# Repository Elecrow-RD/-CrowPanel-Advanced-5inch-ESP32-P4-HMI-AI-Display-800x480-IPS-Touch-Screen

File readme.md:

### 1, Product picture

### 2, Product version number

|      | Hardware | Software | Remark |
| ---- | -------- | -------- | ------ |
| 1    | V1.0     | V1.0     | latest |

### 3, product information

| **Main Chip-ESP32-P4NRW32**                  |                                                              |
| -------------------------------------------- | ------------------------------------------------------------ |
| CPU/SoC                                      | **ESP32-P4**RISC-V 32-bit dual-core processor for HP systems, running at up to 400 MHz;RISC-V 32-bit single-core processor for LP systems, running at up to 40 MHz |
| System Memory                                | 768 KB L2MEM (HP) 32 KB SRAM (LP) 8 KB TCM 32 MB PSRAM       |
| Memory                                       | 128 KB ROM (HP) 16 KB ROM (LP) 16 MB Flash                   |
| Development Environment                      | ESP-IDF、Arduino IDE                                         |
| **Screen**                                   |                                                              |
| Size                                         | 5.0 inch                                                     |
| Resolution                                   | 800*480                                                     |
| Display Panel                                | IPS Panel                                                    |
| Touch Panel                                  | Capacitive Touch, Single/5-point Touch                       |
| Viewing Angle                                | 178°                                                         |
| Brightness                                   | 400 cd/m²(Typ.)                                              |
| Color Depth                                  | 16.7M (8-bit)                                                |
| **Wireless Communication - Onboard Antenna** |                                                              |
| WiFi                                         | Support 2.4GHz(Wi-Fi6), 802.11a/b/g/n                        |
| Bluetooth                                    | Support Bluetooth 5.3 and BLE                                |
| Other                                        | Zigbee, LoRa, nRF2401, Matter, Thread (**Optional**)         |
| **Interface/Function**                       |                                                              |
| Interface                                    | USB2.0, UART, I2C, GPIO female headers, SD card holder, battery socket, speaker jack, camera header, module female headers, etc. |
| Function                                     | Audio amplifier, battery charge management, USB to UART, dual microphones, dual speakers etc. |
| **Button/LED Indicator**                     |                                                              |
| Reset Button                                 | Yes, press to reset the device                               |
| Boot Button                                  | Yes, press and hold the power button to burn the program     |
| Power Button                                 | Switch On/Off                                                |
| PWR                                          | Device power on/off indication                               |
| CHG                                          | Lithium battery charging status, Low battery state           |
| **Other**                                    |                                                              |
| Installation method                          | All around mounting holes(M3 3.2mm), embedded, shell assembly |
| Operating temperature                        | -20~70 °C                                                    |
| Storage temperature                          | -30~80 °C                                                    |
| Power Input                                  | 5V/2A, USB or UART terminal                                  |
| Active Area                                  | 155mm*87mm                                                   |
| Dimensions                                   | 180*105mm                                                    |

### Functional description of the product's internal interfaces:

| Pin Name | Description                                                  | Connector Type |
| :------- | :----------------------------------------------------------- | :------------- |
| SPK      | Output audio signals to connect to speakers. The main board comes with a power amplifier chip circuit. | PH2.0-2P       |
| PWR      | Power LED.                                                   |                |
| RST      | Reset button. Press it to reset the system.                  |                |
| boot     |                                                              |                |
| UART1    | Builds communication between Logic modules, including the serial communication module and the print module. | HY2.0-4P       |
| I2C      | Builds communication between Logic modules, including the serial communication module and the print module. | HY2.0-4P       |
| UART3-IN | Input power supply and serial communication functionality    | XH2.54-4P      |
| BAT      | Connect the lithium battery. (with battery charging circuit) | PH2.0-2P       |

### 4, Use the driver module

| Name | dependency library |
| ---- | ------------------ |
| LVGL | lvgl/lvgl@9.1      |

### 5,Quick Start

##### ESP-IDF starts

1.Right-click on an empty space in the project folder and select "Open with VS Code" to open the project.

2.In the IDF plug-in, select the port, then compile and flash

### 6,Folder structure.
|--3D file： Contains 3D model files (.stp) for the hardware. These files can be used for visualization, enclosure design, or integration into CAD software.

|--Datasheet: Includes datasheets for components used in the project, providing detailed specifications, electrical characteristics, and pin configurations.

|--Eagle_SCH&PCB: Contains **Eagle CAD** schematic (`.sch`) and PCB layout (`.brd`) files. These are used for circuit design and PCB manufacturing.

|--example: Provides example code and projects to demonstrate how to use the hardware and libraries. These examples help users get started quickly.

|--factory_firmware: Stores pre-compiled factory firmware that can be directly flashed onto the device. This ensures the device runs the default functionality.

|--factory_sourcecode:  Contains the source code for the factory firmware, allowing users to modify and rebuild the firmware as needed.

|--libraries: Includes necessary libraries required for compiling and running the project. These libraries provide drivers and additional functionalities for the hardware.

### 7,Pin definition
ESP32-P4 5 inch and IPS Display Wiring Pins:

RGB Pin connection

// Refresh Rate = 18000000/(1+40+20+800)/(1+10+5+480) = 42Hz

#define RGB_LCD_PIXEL_CLOCK_HZ     (18 * 1000 * 1000)

#define RGB_LCD_H_RES              H_size

#define RGB_LCD_V_RES              V_size

#define RGB_LCD_HSYNC              4

#define RGB_LCD_HBP                8

#define RGB_LCD_HFP                8

#define RGB_LCD_VSYNC              4

#define RGB_LCD_VBP                16

#define RGB_LCD_VFP                16

#define RGB_PIN_NUM_DISP_EN        -1

#define RGB_PIN_NUM_HSYNC          40

#define RGB_PIN_NUM_VSYNC          41

#define RGB_PIN_NUM_DE             2

#define RGB_PIN_NUM_PCLK           3

//B

#define RGB_PIN_NUM_DATA0          8

#define RGB_PIN_NUM_DATA1          7

#define RGB_PIN_NUM_DATA2          6

#define RGB_PIN_NUM_DATA3          5

#define RGB_PIN_NUM_DATA4          4

//G

#define RGB_PIN_NUM_DATA5          14

#define RGB_PIN_NUM_DATA6          13

#define RGB_PIN_NUM_DATA7          12

#define RGB_PIN_NUM_DATA8          11

#define RGB_PIN_NUM_DATA9          10

#define RGB_PIN_NUM_DATA10         9

//R

#define RGB_PIN_NUM_DATA11         19

#define RGB_PIN_NUM_DATA12         18

#define RGB_PIN_NUM_DATA13         17

#define RGB_PIN_NUM_DATA14         16

#define RGB_PIN_NUM_DATA15         15

#### ESP32-P4 and Touch Driver Wiring：

i2c address: 0x5D/0x14.(The INT pin level during reset of the GT911 touch chip determines the device address.)

INT Low Level(0x5D);

INT High Level(0x14).

Pin connection

I2C1_SCL(IO46)

I2C1_SDA(IO45)

TP_INT_IO42(IO42)

TP_RST(IO36)

TP_RST_P12(STC8P1.2)

#### ESP32-P4 and wireless module wiring pins：
Output voltage: 3.3V Output current: 1A max. Use: The power supply communicates with the wireless module.

Pin connection

#define RADIO_GPIO_CLK 26

#define RADIO_GPIO_MISO 47

#define RADIO_GPIO_MOSI 48

#ifdef CONFIG_BSP_SX1262_ENABLED

#define SX1262_GPIO_BUSY 29

#define SX1262_GPIO_IRQ 31

#define SX1262_GPIO_NRST 32

#define SX1262_GPIO_NSS 30

#ifdef CONFIG_BSP_NRF2401_ENABLED

#define NRF24_GPIO_IRQ 29

#define NRF24_GPIO_CE 31

#define NRF24_GPIO_CS 32

#### ESP32-P4 and Audio out：

Pin connection

I2S_LRCK(IO21);

I2S_SCLK(IO22);

I2S_SDOUT(IO23);  
#### Function Selection
When the DIP switch is set to position 1, the UART1 function is enabled. When switched to NO, the wireless module function is enabled.

1	ON
UART1	Wireless Module

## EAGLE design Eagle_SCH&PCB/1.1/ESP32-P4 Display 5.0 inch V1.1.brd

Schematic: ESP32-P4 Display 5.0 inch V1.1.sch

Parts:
C1, C2, C3, C17, C22, C102: 1uF; 0603
C4, C12, C28, C70, C74, C78, C79, C83, C88, C136, C157: 10uF; 0603
C5, C7, C9, C25, C36, C39, C40, C41, C43, C45, C46, C50, C53, C60, C61, C63, C73, C108, C113, C115: 100nF; C0402
C6, C8, C42, C44, C47, C48, C49, C56, C71, C107, C112, C114, C116: 10uF; C0402
C10, C69, C86: 1uF; CROWPANEL_ADVANCE_HMI_C0402
C11, C15, C35, C54, C76, C81, C84, C151, C158, C159, C161, C163: 100nF; CROWPANEL_ADVANCE_HMI_C0402
C13, C18: 22uF; C0805
C14, C160, C162: 10uF; CROWPANEL_ADVANCE_HMI_C0402
C19, C75, C77, C80, C82, C144, C155, C156: 100nF; 0603
C23, C24, C103, C104: 47uF; RC_C0805
C26, C31: 22pF; CROWPANEL_ADVANCE_HMI_C0402
C27, C32, C149, C153: 10uF; COOPER_0603
C29, C30: 12pF; C0402
C33, C34, C87: 15pF; C0402
C51, C55, C57, C58, C59, C64, C65, C66, C89: 1uF; C0402
C62: 10nF; C0402
C67, C68, C105, C106: 1nF; 0603
C85: 1nF; COOPER_0603
C150, C152: 100nF; COOPER_0603
D1: KT-0603RYG; LED_KT-0603RYG
D2, D003, D007, D10: DSS34; D_SOD123FL
D4, D008: 1N5819WS; D_SOD323
D11: 1N5819WS 35.384346875; D_SOD323
D14: Red; LED0603
FB1: 0R/800mA; L0402
FB2, FB3, FB10, FB11: 1K/磁珠_NC; L0603
FB16: 0R/800mA_NC; L0603
FB17, FB18, FB19, FB20: 0R/800mA; L0603
FPC2: FPC-6PIN-0.5MM
FPC3: AFC24-S24FIA-00; FPC-SMD_P0.50-24P_QCHF-SM-H2.0
IC1: ESP32-C6-MINI-1-N4; ESP32C6MINI1N4
IC2: ME6211C18M5G-N; SOT95P282X145-5N
IC3: ME6211C28M5G-N; SOT95P282X145-5N
IC4: W25Q128JVSIQ; SOIC127P790X216-8N
IC7, IC8: ME6211C33M5G-N; SOT95P282X145-5N
J1, J16: TYPEC-3.0-16P-SMD; USB-3.0TYPEC-SMD
J2, J13: HY2.0-4P-SMT; CONNECTOR_4P-SMD-2.0
J3, J4, J6: PH2.0WT-2PIN
J5: HOLDER-MICROSD-9P; 9P-SMD-W/-RING
J7: CONN_8X2_SMD; 2X8_SMD
J8: HC-PZ200-8.7L-1X4PZ1; TEST-PIN-4-2.0MM
J9, J11: HEADER-7P-18.28X2.5; H7-2.54-18.28X2.5X5MM
J10: XH2.54-4P-SMT; XH2.54-4P-SMD
J12, J14, J15, J17: CROWPANEL_ADVANCE_HMI_THO-M3.25MM-HOLE; CROWPANEL_ADVANCE_HMI_THO-M3.2*5MM-HOLE
JP1: FPC-0.5MM-40PIN; CROWPANEL_ADVICE_HMI-4.3_COOPER_0.5MM*40P
K3, K4: KEY-4.5X4.5; KEY-4.5X4.5-SMD
L1, L6: 2.2μH_C5179446; 1008(2520)
L4: 0R; L0603
L5: 4.7uH_C45385206_2.4A; 1008(2520)
P1, P2, P3, P4, P5, P6, P7, P8, P9, P10, P11, P12, P13, P14, P15, P16, P17, P18, P19, P20, P21, P22, P23, P24, P25, P26, P27, P28, P29, P30, P31, P32, P33, P34, P35, P36, P37, P38, P39, P40, P41, P42, P43, P44, P45, P46, P47, P48, P49, P50, P51, P52, P53, P54, P55, P56, P57, P58, P59, P60, P61, P62, P63, P64, P65, P66, P67, P68, P69, P70, P71, P72, P73, P74, P75, P76, P77, P78, P79, P80, P81, P82, P83, P84, P85, P86, P87, P88, P89, P90, P91, P92, P93, P94, P95: TEST_PADPAD-1.5MM; TEST_PAD-1.5MM
Q1, Q2, Q4, Q6, Q7, Q8, Q9: BSS138W_SOT323; MOS_SOT323
Q3, Q5: NCE20P45Q; MY_LIB_PDFN3333
Q10: AO3401; PMOS_SOT23
Q11: AO3401_NC; PMOS_SOT23
R1, R5, R9, R15, R18, R27, R28, R29, R30, R54, R61, R66, R67, R71, R73, R77, R87, R91, R106, R116, R160, R181: 10K; CROWPANEL_ADVANCE_HMI_R0402
R2, R117, R139: 100K; CROWPANEL_ADVANCE_HMI_R0402
R3, R4, R96, R101: 5.1K; CROWPANEL_ADVANCE_HMI_R0402
R6, R7, R8, R10, R13, R48, R49, R55, R60, R69, R72, R88, R89, R90, R103, R112, R113, R114, R115, R118, R119, R129, R149, R192: 0R; CROWPANEL_ADVANCE_HMI_R0402
R11: 22.1K; CROWPANEL_ADVANCE_HMI_R0402
R12, R19, R20, R23, R25, R36, R37, R38, R39, R40, R41, R42, R43, R44, R63, R64, R70, R80, R95, R105, R111, R133, R135: 0R; R0402
R14, R21: NC/499K; CROWPANEL_ADVANCE_HMI_R0402
R16, R32: 2K; R0603-SP
R17, R26, R47, R50: 5.1K; R0603
R22, R45, R46, R51, R52, R56, R57, R58, R59, R62, R78, R93, R94, R97, R98: 4.7K; R0603
R24, R76, R92, R184: 0R; R0603
R31, R74: 27K; R0603-SP
R33, R79, R180: NC; CROWPANEL_ADVANCE_HMI_R0402
R34, R109, R110, R122, R176: NC; R0402
R35: NC/10M; R0402
R53: 2K; COOPER_R0603
R65, R191: 10K; R0402
R68, R99, R100, R188, R189: 22R; R0402
R75: NC; R0603
R81, R82, R83, R84, R85, R86: 51K; CROWPANEL_ADVANCE_HMI_R0402
R107: 0R_NC; R0402
R120, R121: 5.1K_NC; R0603
R143: 47K; CROWPANEL_ADVANCE_HMI_R0402
R152, R153, R154, R155, R156, R157: 100R; R0402
R158: 4.02K; R0402
R159: 3.6R; R0603-SP
R164: 39k; CROWPANEL_ADVANCE_HMI_R0402
R183: 0R; R0603-SP
R186: 100k; CROWPANEL_ADVANCE_HMI_R0402
R187: 10k; CROWPANEL_ADVANCE_HMI_R0402
R210: NC/10K; CROWPANEL_ADVANCE_HMI_R0402
S1: DSIC-01-TS-GER; SW_SMD2_DSIC-01-TS-GER
SW1: switch_6pin; SWITCH_6PIN_2P
U1: CH340K; ESOP-10-EP-150MIL
U2: TP4059-SOT23-6; SOT23-6L
U3, U13: NS4168; NS4168-ESOP-8
U5: SGM3005XMSTR; MSOP-10
U6: MT9201; COOPER_SOT23-6
U7: ESP32-P4NRW32; IC_ESP32-P4NRW32
U8: UMH3NTN; SOP65P210X100-6N
U9, U10: MT3406_C22462728; SOT95P280X145-5N
U14: STC8H1K17-36I; TSSOP20
U175: MMICT5838-00-012_LMD3526B261-OFA03; MMICT5838-00-012_MIC-SMD_5P-L3.5-W2.7-P1.67
Y2: 40MHZ; X322540MPB4SI
Y3: 24Mhz; 24MHZ_1631-24003-BTKEYA
Y4: 32.768K; NORDIC_NRF_XTAL_3215_N

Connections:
3V3$: C2.2, U1.10 (V3)
13: R189.1, U14.3 (MISO/P1.4)
14: R188.1, U14.4 (SCLK/P1.5)
+5V_IN: D2.+, D4.+, J10.3, P63.P$1, R46.1, R51.1
+VBUS1: D10.+, D11.+, J1.A4, J1.A9, J1.B4, J1.B9, P1.P$1
+VBUS2: D007.+, D008.+, J16.A4, J16.A9, J16.B4, J16.B9
ADC_VBAT: C158.2, R164.2, R186.1, U14.13 (P3.2/ADC10)
AGND: C102.2, C103.2, C104.2, C105.1, C106.1, FB19.2, J4.P$3, J4.P$4, R143.2, U13.7 (GND), U13.9 (PE)
AGND1: C25.1, R176.2, R183.2, U175.5_1 (GND), U175.5_2 (GND)
AGND3: C22.2, C23.2, C24.2, C67.1, C68.1, FB20.2, J6.P$3, J6.P$4, U3.7 (GND), U3.9 (PE)
AUDIO_CTRL: Q10.3 (D), R117.1, R139.1
AUDIO_OUT_SD_P10: Q10.1 (G), R71.1, U14.19 (P1.0/ADC0)
AUDIO_VDD1: C102.1, C103.1, C104.1, FB17.1, U13.6 (VDD)
AUDIO_VDD2: C22.1, C23.1, C24.1, FB18.1, U3.6 (VDD)
AUDIO_VDD_3V3: C152.2, C153.2, FB1.1, FB16.2, IC7.5 (VOUT)
AVDD_2V8: C82.2, C83.2, FPC3.1, FPC3.2, IC3.5 (VOUT)
C6_EN_IO20: C15.1, IC1.8 (EN), R77.1, R95.2
C6_IO8: IC1.22 (IO8), R87.2
C6_IO9_BOOT: IC1.23 (IO9), P36.P$1, P87.P$1
C6_RXD0: IC1.30 (RXD0), P21.P$1, P88.P$1
C6_TXD0: IC1.31 (TXD0), P25.P$1, P89.P$1
C6_VDD_3V3: C11.1, C14.2, IC1.3 (3V3), P37.P$1, P86.P$1, R76.1, R77.2, R81.1, R82.1, R83.1, R84.1, R85.1, R86.1, R87.1
CSID0_P: R153.1, U7.43 (CSI_DATAP0)
CSI_CLK_N: FPC3.19, R156.2
CSI_CLK_P: FPC3.18, R157.2
CSI_D0_N: FPC3.16, R152.2
CSI_D0_P: FPC3.15, R153.2
CSI_D1_N: FPC3.22, R154.2
CSI_D1_P: FPC3.21, R155.2
CSI_RESET: FPC3.8, Q4.2 (S), R57.2
CSI_RESET_P13: Q4.3 (D), R58.2, U14.2 (MOSI/P1.3)
CSI_SCL: FPC3.4, Q7.2 (S), R62.2
CSI_SDA: FPC3.5, Q6.2 (S), R56.2
DA1: J5.8 (DATA1), R15.1
DA2: J5.1 (DATA2), R30.1
DOVDD_1V8: C77.2, C78.2, C84.2, C85.2, FPC3.9, IC2.5 (VOUT), Q4.1 (G), Q6.1 (G), Q7.1 (G), R56.1, R57.1, R62.1, R67.2, Y3.4 (4_VDD)
DOWNLOAD_BOOT: R60.1, R69.2, R106.2
DTR: R5.2, U1.4 (DTR#), U8.4 (E2)
EN_DCDC: R13.2, U7.79 (EN_DCDC)
ESP32_LDO1: C58.1, R105.2, U7.71 (VFB1/VO1)
ESP32_LDO2: C57.1, R40.2, U7.72 (VFB2/VO2)
ESP32_LDO3: C59.1, R80.2, U7.73 (VFB3/VO3)
ESP32_LDO4: C66.1, R109.2, U7.74 (VFB4/VO4)
FB_DCDC: C31.1, R14.2, R21.1, R103.1, U10.5 (FB)
FLASH_CK: IC4.6 (CLK), U7.32 (FLASH_CK)
FLASH_CS: IC4.1 (/CS), R65.1, U7.27 (FLASH_CS)
FLASH_D: IC4.5 (DI_(IO0)), U7.33 (FLASH_D)
FLASH_HOLD: IC4.7 (/HOLD_OR_/RESET_(IO3)), U7.31 (FLASH_HOLD)
FLASH_Q: IC4.2 (DO_(IO1)), U7.28 (FLASH_Q)
FLASH_WP: IC4.3 (/WP_(IO2)), U7.29 (FLASH_WP)
GND: C1.1, C2.1, C3.1, C4.1, C5.2, C6.1, C7.2, C8.1, C9.2, C10.1, C11.2, C12.2, C13.2, C14.1, C15.2, C17.1, C18.2, C19.2, C27.1, C28.2, C29.2, C30.2, C32.1, C33.2, C34.1, C35.1, C36.2, C39.2, C40.2, C41.2, C42.1, C43.2, C44.1, C45.2, C46.2, C47.1, C48.1, C49.1, C50.2, C51.2, C53.1, C54.1, C55.2, C56.1, C57.2, C58.2, C59.2, C60.2, C61.2, C62.2, C63.2, C64.2, C65.2, C66.2, C69.1, C70.2, C71.1, C73.2, C74.1, C75.1, C76.1, C77.1, C78.1, C79.1, C80.1, C81.1, C82.1, C83.1, C84.1, C85.1, C86.1, C87.2, C88.2, C89.1, C107.1, C108.2, C112.1, C113.2, C114.1, C115.2, C116.1, C136.1, C144.1, C149.1, C150.1, C151.1, C152.1, C153.1, C155.1, C156.1, C157.1, C158.1, C159.1, C160.1, C161.1, C162.1, C163.1, D14.-, FB19.1, FB20.1, FPC2.4, FPC2.7, FPC2.8, FPC3.3, FPC3.6, FPC3.10, FPC3.12, FPC3.17, FPC3.20, FPC3.25, FPC3.26, IC1.1 (GND_1), IC1.2 (GND_2), IC1.11 (GND_3), IC1.14 (GND_4), IC1.36 (GND_5), IC1.37 (GND_6), IC1.38 (GND_7), IC1.39 (GND_8), IC1.40 (GND_9), IC1.41 (GND_10), IC1.42 (GND_11), IC1.43 (GND_12), IC1.44 (GND_13), IC1.45 (GND_14), IC1.46 (GND_15), IC1.47 (GND_16), IC1.48 (GND_17), IC1.49 (GND_18), IC1.50 (GND_19), IC1.51 (GND_20), IC1.52 (GND_21), IC1.53 (GND_22), IC1.54 (GND_23), IC1.55 (GND_24), IC1.56 (GND_25), IC1.57 (GND_26), IC1.58 (GND_27), IC1.59 (GND_28), IC1.60 (GND_29), IC1.61 (GND_30), IC2.2 (VSS), IC3.2 (VSS), IC4.4 (GND), IC7.2 (VSS), IC8.2 (VSS), J1.A1, J1.A12, J1.B1, J1.B12, J1.P$1, J1.P$2, J1.P$3, J1.P$4, J2.4, J2.SS1, J2.SS2, J3.P$2, J3.P$3, J3.P$4, J5.6 (VSS), J5.G1, J5.G2, J5.G3, J5.G4, J7.11, J7.13, J7.14, J7.15, J7.16, J8.4, J9.6, J9.6-6 (6), J10.4, J10.5 (SS1), J10.6 (SS2), J12.P$1, J13.4, J13.SS1, J13.SS2, J14.P$1, J15.P$1, J16.A1, J16.A12, J16.B1, J16.B12, J16.P$1, J16.P$2, J16.P$3, J16.P$4, J17.P$1, JP1.P$5 (GND2), JP1.P$12 (GND4), JP1.P$18 (B2), JP1.P$19 (B1), JP1.P$20 (B0), JP1.P$27 (G1), JP1.P$28 (G0), JP1.P$34 (R2), JP1.P$35 (R1), JP1.P$36 (R0), JP1.P$38 (GND3), JP1.P$41 (GND5), JP1.P$42 (GND6), K3.1, K4.1, P4.P$1, P10.P$1, P12.P$1, P28.P$1, P30.P$1, P31.P$1, P60.P$1, P70.P$1, P71.P$1, P76.P$1, P80.P$1, P81.P$1, P85.P$1, P90.P$1, P95.P$1, R3.1, R4.2, R11.2, R16.1, R18.1, R21.2, R33.2, R73.1, R74.2, R96.1, R101.2, R158.2, R159.1, R160.2, R183.1, R186.2, SW1.1 (1_2B), SW1.6 (6_1B), U1.3 (GND), U1.EP, U2.2 (GND), U5.6 (GND), U6.2 (2-GND), U7.105 (GND), U9.2 (GND), U10.2 (GND), U14.10 (GND), Y2.2 (GND_1), Y2.4 (GND_2), Y3.2 (2_GND)
I2C1_SCL: P18.P$1, Q9.2 (S), R64.2, R97.2, U7.88 (GPIO46)
I2C1_SCL_3V3: J11.2, J11.2-2 (2), J13.1, P62.P$1, Q9.3 (D), R93.2, R188.2
I2C1_SDA: P19.P$1, Q8.2 (S), R63.2, R98.2, U7.87 (GPIO45)
I2C1_SDA_3V3: J11.3, J11.3-3 (3), J13.2, P61.P$1, Q8.3 (D), R94.2, R189.2
I2C2_SCL: Q7.3 (D), R59.2, U7.65 (GPIO34)
I2C2_SDA: Q6.3 (D), R22.2, U7.64 (GPIO33)
I2SOUT_LRCK1: R149.2, U13.2 (LRCLK)
I2SOUT_LRCK2: P35.P$1, R114.2, U3.2 (LRCLK)
I2SOUT_SCLK1: R129.2, U13.3 (BCLK)
I2SOUT_SCLK2: P34.P$1, R113.2, U3.3 (BCLK)
I2SOUT_SD1: R112.2, U13.4 (SDATA)
I2SOUT_SD2: P33.P$1, R115.2, U3.4 (SDATA)
I2S_LRCK: R114.1, R149.1, U7.23 (GPIO21)
I2S_SCLK: R113.1, R129.1, U7.24 (GPIO22)
I2S_SDOUT: R112.1, R115.1, U7.25 (GPIO23)
IO29_W: J7.6, J11.5, J11.5-5 (5), P23.P$1, U7.58 (GPIO29)
IO30_W_BUSY: J7.8, J11.6, J11.6-6 (6), P22.P$1, U7.60 (GPIO30)
LCD_3V3: C160.2, C161.2, C162.2, C163.2, FPC2.5, JP1.P$37 (VCC), P40.P$1, P72.P$1, R92.1, R191.2
LCD_B3_IO8: JP1.P$17 (B3), P52.P$1, U7.8 (GPIO8)
LCD_B4_IO7: JP1.P$16 (B4), P53.P$1, U7.7 (GPIO7)
LCD_B5_IO6: JP1.P$15 (B5), P56.P$1, U7.6 (GPIO6)
LCD_B6_IO5: JP1.P$14 (B6), P57.P$1, U7.5 (GPIO5)
LCD_B7_IO4: JP1.P$13 (B7), P65.P$1, U7.4 (GPIO4)
LCD_BK_EN_P11: R72.1, U14.20 (P1.1/ADC1)
LCD_BK_POWER_P37: R79.1, R180.1, U14.18 (P3.7/INT3)
LCD_BK_VDD: C13.1, C17.2, L5.1, Q11.3 (D), R184.2, U6.6 (6-VIN)
LCD_CLK_IO3: JP1.P$11 (CLK), P66.P$1, R68.2
LCD_DE_IO2: JP1.P$7 (DE), P69.P$1, U7.2 (GPIO2)
LCD_G2_IO14: JP1.P$26 (G2), P46.P$1, U7.15 (GPIO14)
LCD_G3_IO13: JP1.P$25 (G3), P47.P$1, U7.14 (GPIO13)
LCD_G4_IO12: JP1.P$24 (G4), P48.P$1, U7.13 (GPIO12)
LCD_G5_IO11: JP1.P$23 (G5), P49.P$1, U7.12 (GPIO11)
LCD_G6_IO10: JP1.P$22 (G6), P50.P$1, U7.11 (GPIO10)
LCD_G7_IO9: JP1.P$21 (G7), P51.P$1, U7.10 (GPIO9)
LCD_HSYNC_IO40: JP1.P$9 (HSYNC), P67.P$1, U7.81 (GPIO40)
LCD_LED+: C18.1, C19.1, D003.-, JP1.P$39 (LEDA), P39.P$1, U6.5 (5-OV)
LCD_LED-: JP1.P$40 (LEDK), P38.P$1, R159.2, U6.3 (3-FB)
LCD_R3_IO19: JP1.P$33 (R3), P41.P$1, U7.20 (GPIO19)
LCD_R4_IO18: JP1.P$32 (R4), P42.P$1, U7.19 (GPIO18)
LCD_R5_IO17: JP1.P$31 (R5), P43.P$1, U7.18 (GPIO17)
LCD_R6_IO16: JP1.P$30 (R6), P44.P$1, U7.17 (GPIO16)
LCD_R7_IO15: JP1.P$29 (R7), P45.P$1, U7.16 (GPIO15)
LCD_VSYNC_IO41: JP1.P$8 (VSYNC), P68.P$1, U7.82 (GPIO41)
MIC1_1: R133.2, U175.1 (DATA)
MIC1_2: R34.1, R176.1, U175.2 (L/R)
MIC1_3: R135.1, U175.3 (CLK)
MIC1_VDD_3V3: C25.2, FB1.2, R34.2, U175.4 (VDD)
MIC_MCLK1_IO24: P27.P$1, R135.2, U7.52 (GPIO24)
MIC_SD1_IO25: P29.P$1, R133.1, U7.53 (GPIO25)
unnamed: R1.1, U9.1 (EN)
unnamed: L1.1, U9.3 (SW)
unnamed: R55.2, U7.66 (GPIO35)
unnamed: FB10.1, U13.8 (VOP)
unnamed: R6.1, U1.1 (UD+)
unnamed: R7.1, U1.2 (UD-)
unnamed: R5.1, U8.2 (B1)
unnamed: R9.1, U8.5 (B2)
unnamed: J1.B5, R3.2
unnamed: R8.2, U1.9 (RXD)
unnamed: R10.2, U1.8 (TXD)
unnamed: R16.2, U2.6 (PRO)
unnamed: C26.1, R2.2, R11.1, U9.5 (FB)
unnamed: L6.1, U10.3 (SW)
unnamed: C151.2, IC7.3 (CE), R181.1
unnamed: R13.1, R210.2, U10.1 (EN)
unnamed: FPC2.1, R64.1
unnamed: FPC2.2, R63.1
unnamed: D1.3, R31.1, R121.1
unnamed: D1.4, R32.1, R120.1
unnamed: D14.+, R26.1
unnamed: C159.2, R187.2, R192.2, U14.7 (NRST/PWM6/P5.4)
unnamed: J9.1, J9.1-1 (1), R49.1
unnamed: J11.1, J11.1-1 (1), R48.1
unnamed: C30.1, R35.1, U7.1 (GPIO1), Y4.2
unnamed: Q5.4 (4_G), R78.1, SW1.2 (2_COM2), SW1.5 (5_COM1)
unnamed: J1.A5, R4.1
unnamed: Q11.1 (G), R79.2
unnamed: C28.1, R24.1, R210.1, U10.4 (VIN)
unnamed: C29.1, R35.2, U7.104 (GPIO0), Y4.1
unnamed: JP1.P$10 (DISP), R191.1
unnamed: R68.1, U7.3 (GPIO3)
unnamed: R72.2, R160.1, U6.4 (4-EN)
unnamed: R99.2, U7.49 (DM)
unnamed: R100.2, U7.50 (DP)
unnamed: R95.1, U7.22 (GPIO20)
unnamed: R103.2, U7.78 (FB_DCDC)
unnamed: FB2.1, U3.8 (VOP)
unnamed: FB11.1, U13.5 (VON)
unnamed: FB3.1, U3.5 (VON)
unnamed: R117.2, U3.1 (CTRL)
unnamed: R118.2, U14.12 (P3.1/ADC9)
unnamed: R119.2, U14.11 (P3.0/ADC8)
unnamed: R139.2, R143.1, U13.1 (CTRL)
unnamed: C155.2, IC8.3 (CE), R116.1
unnamed: R158.1, U7.48 (CSI_REXT)
unnamed: R157.1, U7.44 (CSI_CLKP)
unnamed: R156.1, U7.45 (CSI_CLKN)
unnamed: R155.1, U7.47 (CSI_DATAP1)
unnamed: R154.1, U7.46 (CSI_DATAN1)
unnamed: R152.1, U7.42 (CSI_DATAN0)
unnamed: J16.B5, R96.2
unnamed: J16.A5, R101.1
unnamed: C76.2, IC2.3 (CE), R61.1
unnamed: C81.2, IC3.3 (CE), R66.1
unnamed: C86.2, R67.1, Y3.1 (1_EN)
unnamed: D003.+, L5.2, U6.1 (1-SW)
P4_IO36: R60.2, U7.68 (GPIO36)
P4_IO39: R90.2, U7.80 (GPIO39)
P4_IO43: R88.2, U7.84 (GPIO43)
P4_IO44: R89.2, U7.86 (GPIO44)
P4_RST_EN: C35.2, K4.2, R54.2, R192.1, U7.103 (CHIP_PU), U8.6 (C1)
P4_RXD1_IO48: J2.1, P79.P$1, U5.5 (NC1)
P4_RXD2_IO32: J7.12, P59.P$1, R48.2, U7.63 (GPIO32)
P4_TXD1_IO47: J2.2, P78.P$1, U5.7 (NC2)
P4_TXD2_IO31: J7.10, P58.P$1, R49.2, U7.61 (GPIO31)
P4_VBAT: C9.1, C42.2, R20.1, U7.102 (VBAT)
POWER_CHRG: R50.1, R120.2, U2.1 (CHG), U14.14 (P3.3/ADC11)
POWER_DONE: R47.1, R121.2, U2.5 (STD), U14.15 (P3.4/ADC11)
POWER_G_LED: R31.2, U14.17 (P3.6/ADC14)
POWER_R_LED: R32.2, U14.16 (P3.5/ADC13)
RTS: R9.2, U1.6 (RTS#), U8.1 (E1)
RXD0: R10.1, U7.70 (GPIO38)
RXD1_MOSI_IO48: J7.9, U5.3 (COM1), U7.90 (GPIO48)
RXD3: Q2.2 (S), R45.2, U7.57 (GPIO28)
SD1_CMD_IO44: J5.3 (DI), P8.P$1, P92.P$1, R28.1, R89.1
SD1_D0_IO39: J5.7 (DO), P6.P$1, P94.P$1, R27.1, R90.1
SD1_SCK_IO43: J5.5 (SCLK), P7.P$1, P93.P$1, R88.1
SD2_CLK: IC1.25 (IO19), R82.2, U7.97 (GPIO53)
SD2_CMD: IC1.24 (IO18), R81.2, U7.98 (GPIO54)
SD2_D0: IC1.26 (IO20), R83.2, U7.95 (GPIO52)
SD2_D1: IC1.27 (IO21), R84.2, U7.94 (GPIO51)
SD2_D2: IC1.28 (IO22), R85.2, U7.93 (GPIO50)
SD2_D3: IC1.29 (IO23), R86.2, U7.92 (GPIO49)
SDCS: J5.2 (CS), R29.1, R33.1
SEL0: R53.2, R73.2, S1.2, U5.4 (IN1), U5.8 (IN2)
SPI2_MISO_IO47: J9.3, J9.3-3 (3), P15.P$1, U5.10 (NO2)
SPI2_MOSI_IO48: J9.4, J9.4-4 (4), P14.P$1, U5.2 (NO1)
SPI2_SCK_IO26: J7.5, J9.2, J9.2-2 (2), P16.P$1, U7.55 (GPIO26)
SPI_BOOT: C54.2, K3.2, R55.1, R91.2, U8.3 (C2)
STC8_RXD: J8.2, P83.P$1, R119.1
STC8_TXD: J8.1, P82.P$1, R118.1
STC8_VDD_3V3: C69.2, C156.2, C157.2, D1.1, D1.2, IC8.5 (VOUT), J8.3, P84.P$1, R58.1, R187.1, U14.8 (VCC), U14.9 (VREF)
SW_SPI_UART_P17: R53.1, U14.6 (XTALI/P1.7)
TP_INT_IO42: FPC2.3, P20.P$1, R75.2, U7.83 (GPIO42)
TP_RST: FPC2.6, P73.P$1, R74.1, R111.1, R122.1
TP_RST_IO36: R69.1, R111.2
TP_RST_P12: R122.2, U14.1 (SS/P1.2)
TXD0: R8.1, U7.69 (GPIO37)
TXD1_MISO_IO47: J7.7, U5.9 (COM2), U7.89 (GPIO47)
TXD3: Q1.2 (S), R52.2, U7.56 (GPIO27)
UART_IN_RXD3: J10.2, P64.P$1, Q2.3 (D), R46.2
UART_IN_TXD3: J10.1, P74.P$1, Q1.3 (D), R51.2
USB1_D+: J1.A6, J1.B6, P2.P$1, R6.2
USB1_D-: J1.A7, J1.B7, P3.P$1, R7.2
USB2_D+: J16.A6, J16.B6, R100.1
USB2_D-: J16.A7, J16.B7, R99.1
VBAT: C4.2, J3.P$1, P9.P$1, Q3.5 (5_D), Q3.6 (6_D), Q3.7 (7_D), Q3.8 (8_D), Q3.9 (9_D), R17.1, R164.1, U2.3 (BAT)
VCC5V: C136.2, C144.2, D2.-, D007.-, D10.-, IC8.1 (VIN), P11.P$1, Q3.1 (1_S), Q3.2 (2_S), Q3.3 (3_S), Q5.1 (1_S), Q5.2 (2_S), Q5.3 (3_S), R78.2, R116.2
VCC5V_IN: C3.2, D4.-, D008.-, D11.-, Q3.4 (4_G), R17.2, R18.2, R47.2, R50.2, U2.4 (VCC)
VCCA: C43.1, C47.2, R23.1, U7.51 (VCCA)
VDD5V: C12.1, C149.2, C150.2, FB17.2, FB18.2, IC7.1 (VIN), J7.2, J7.4, L4.2, P5.P$1, Q5.5 (5_D), Q5.6 (6_D), Q5.7 (7_D), Q5.8 (8_D), Q5.9 (9_D), Q11.2 (S), R1.2, R24.2, R26.2, R180.2, R181.2, R184.1, U9.4 (VIN)
VDD5V_W: C88.1, J9.7, J9.7-7 (7), L4.1
VDDA: C7.1, C8.2, R19.1, U7.101 (VDDA)
VDDPST: C36.1, C55.1, R40.1, R110.1, U7.59 (VDDPST), U7.67 (VDDPST)
VDDPST_1: C73.1, C107.2, R36.1, U7.9 (VDDPST_1)
VDDPST_2: C41.1, C44.2, R37.1, U7.21 (VDDPST_2)
VDDPST_3: C45.1, C49.2, R38.1, U7.30 (VDDPST_3)
VDDPST_4: C50.1, C56.2, R39.1, U7.62 (VDDPST_4)
VDDPST_5: C60.1, C65.1, Q8.1 (G), Q9.1 (G), R22.1, R25.1, R59.1, R75.1, R97.1, R98.1, R109.1, U7.85 (VDDPST_5)
VDDPST_6: C61.1, C71.2, R41.1, U7.96 (VDDPST_6)
VDDPST_DCDC: C5.1, C6.2, R12.1, U7.77 (VDDPST_DCDC)
VDDPST_LDO: C46.1, C48.2, R70.1, U7.75 (VDDPST_LDO)
VDD_1V2: C31.2, C32.2, L6.2, P24.P$1, R14.1, R42.2, R43.2, R44.2
VDD_3V3: C1.2, C10.2, C26.2, C27.2, C53.2, C70.1, C74.2, C75.2, C79.2, C80.2, C89.2, FB16.1, IC2.1 (VIN), IC3.1 (VIN), J2.3, J5.4 (VDD), J7.1, J7.3, J9.5, J9.5-5 (5), J13.3, L1.2, P13.P$1, P17.P$1, P75.P$1, P77.P$1, P91.P$1, Q1.1 (G), Q2.1 (G), Q10.2 (S), R2.1, R12.2, R15.2, R19.2, R20.2, R23.2, R25.2, R27.2, R28.2, R29.2, R30.2, R36.2, R37.2, R38.2, R39.2, R41.2, R45.1, R52.1, R54.1, R61.2, R66.2, R70.2, R71.2, R76.2, R91.1, R92.2, R93.1, R94.1, R106.1, R107.2, R110.2, S1.1, U1.7 (VCC), U5.1 (V+)
VDD_FLASH: C39.1, C40.1, C51.1, IC4.8 (VCC), R65.2, R105.1, R107.1
VDD_HP_0: C108.1, C112.2, R42.1, U7.26 (VDD_HP_0)
VDD_HP_2: C113.1, C114.2, R43.1, U7.76 (VDD_HP_2)
VDD_HP_3: C115.1, C116.2, R44.1, U7.91 (VDD_HP_3)
VDD_MIPI_DPHY: C62.1, C63.1, C64.1, R80.1, U7.41 (VDD_MIPI_DPHY)
VOLN: C106.2, FB11.2, J4.P$2, P55.P$1
VOLP: C105.2, FB10.2, J4.P$1, P54.P$1
VORN: C68.2, FB3.2, J6.P$2, P32.P$1
VORP: C67.2, FB2.2, J6.P$1, P26.P$1
XTAL_N: C34.2, U7.99 (XTAL_N), Y2.3 (CRYSTAL_2)
XTAL_P: C33.1, U7.100 (XTAL_P), Y2.1 (CRYSTAL_1)
XVCLK: C87.1, FPC3.11, Y3.3 (3_OUT)

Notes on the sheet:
BOOT
RESET
HIG: SPI Boot
LOW: Download Boot
HIG: ESP32-P4 Enable
LOW: ESP32-P4 Off
Power_LED
USB interface
USB TO UART
Battery and control
ESP32-C6
5.0 inch IPS interface
SD card
Wireless module
UART & I2C & GPIO extensions
PDM MIC
UART_5V_IN
I2C_OUT
UART1_OUT
ESP32-P4
ESP32-P4_POWER
CSI_Interface
I led=200mV/3.6=55.5mA
LCD_LED Driver
Audio_OUT
DC-DC:5V to 3V3
DC-DC:5V to 1V2
Power SW
Charge indicator control
LDO:5V to 3V3(AUDIO POWER)
Function switching

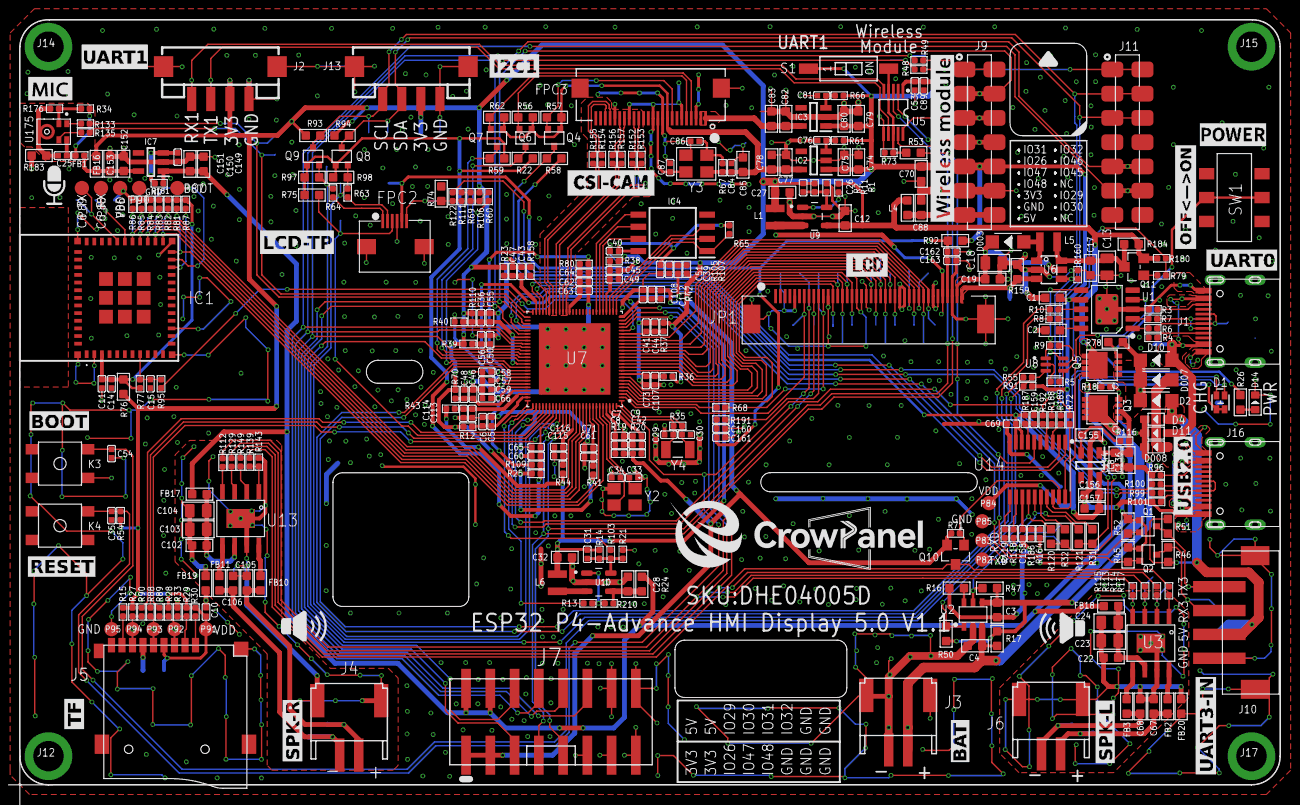
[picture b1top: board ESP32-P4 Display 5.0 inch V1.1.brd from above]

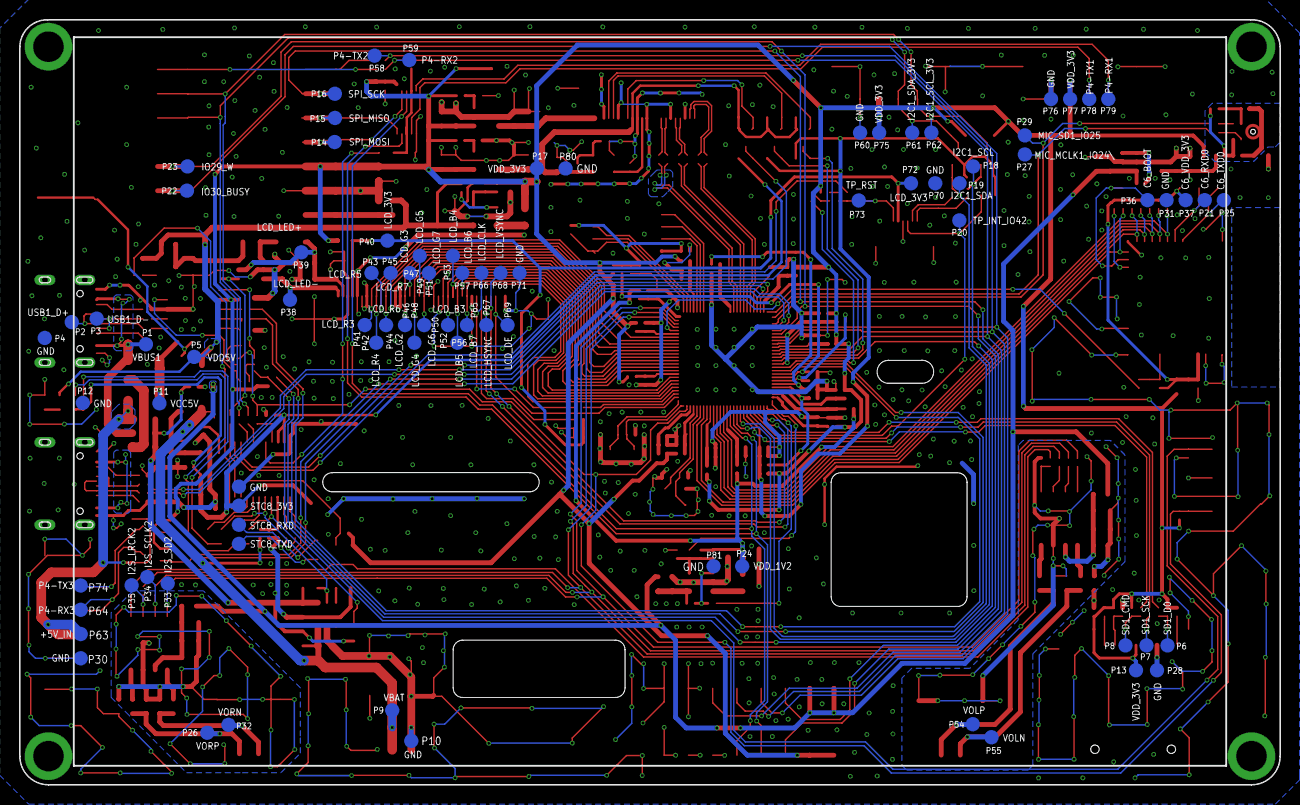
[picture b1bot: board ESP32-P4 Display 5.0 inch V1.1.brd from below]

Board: 2 copper layers, 132.0 x 80.1 mm, 432 parts (82 on the bottom side), 237 nets.

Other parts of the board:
U$113: P4-LCD-7.0-BK3

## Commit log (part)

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2026-03-18 add arduino
2026-05-25 sync idf lesson13
2026-06-08 wifi

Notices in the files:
parts and their libraries:
SparkFun-Coils: Licensing: Creative Commons ShareAlike 4.0 International - https://creativecommons.org/licenses/by-sa/4.0
